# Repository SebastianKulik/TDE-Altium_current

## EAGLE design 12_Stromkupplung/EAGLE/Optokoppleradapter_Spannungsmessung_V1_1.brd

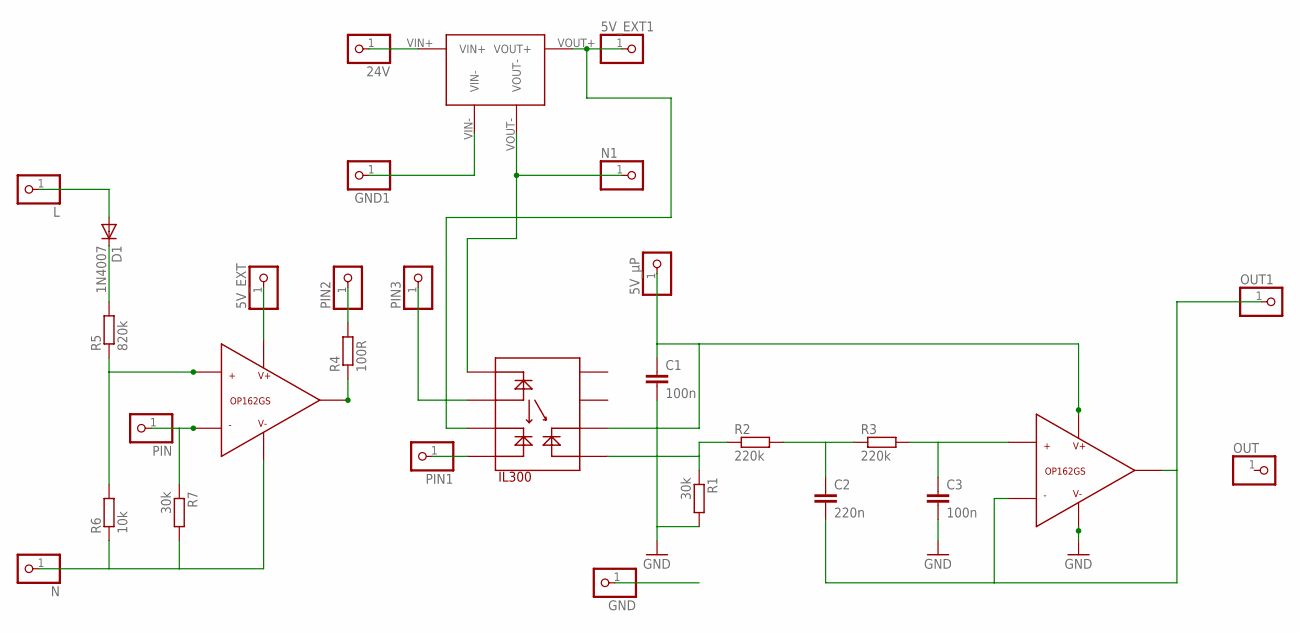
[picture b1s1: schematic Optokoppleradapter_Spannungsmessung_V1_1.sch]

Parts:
5V_EXT, 5V_EXT1, 5V_µP, 24V: PINHD-1X1; 1X01
C1, C3: 100n; C0805
C2: 220n; C0805
D1: 1N4007; DO35-7
GND, GND1: PINHD-1X1; 1X01
L: PINHD-1X1; 1X01
N, N1: PINHD-1X1; 1X01
OUT, OUT1: PINHD-1X1; 1X01
PIN, PIN1, PIN2, PIN3: PINHD-1X1; 1X01
R1: 30k; R0805
R2, R3: 220k; R0805
R4: 100R; R0805
R5: 820k; 0207/7
R6: 10k; 0207/7
R7: 30k; 0207/7
U$1: IL300; DIP8
U$2, U$3: OP162GS; SOIC_N
U$4: RECOM_RO-2405S; 4PIN_SIP

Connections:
5V_EXTERN: 5V_EXT.1, U$2.P$7 (V+)
5V_EXTERN1: 5V_EXT1.1, U$1.P$3, U$4.VOUT+
5V_µP: 5V_µP.1, C1.1, U$1.P$6, U$3.P$7 (V+)
24V: 24V.1, U$4.VIN+
GND: GND.1
GND1: C1.2, C3.2, GND1.1, R1.2, U$3.P$4 (V-), U$4.VIN-
L: D1.A, L.1
N: N.1, R6.1, R7.2, U$2.P$4 (V-)
N1: N1.1, U$1.P$1, U$4.VOUT-
unnamed: D1.C, R5.2
unnamed: R5.1, R6.2, U$2.P$3 (+)
unnamed: PIN1.1, U$1.P$4
unnamed: PIN.1, R7.1, U$2.P$2 (-)
unnamed: R4.1, U$2.P$6 (OUT)
unnamed: PIN2.1, R4.2
unnamed: PIN3.1, U$1.P$2
unnamed: R1.1, R2.1, U$1.P$5
unnamed: C2.1, R2.2, R3.1
unnamed: C3.1, R3.2, U$3.P$3 (+)
OUT1: C2.2, OUT1.1, U$3.P$2 (-), U$3.P$6 (OUT)

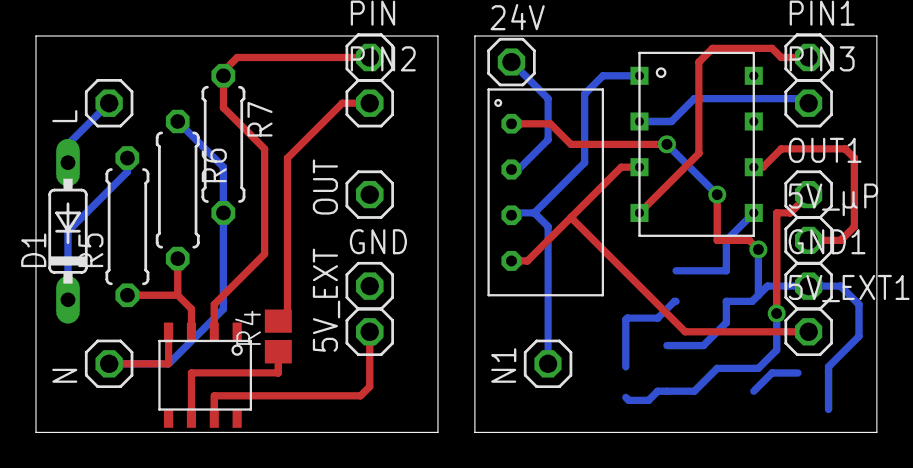
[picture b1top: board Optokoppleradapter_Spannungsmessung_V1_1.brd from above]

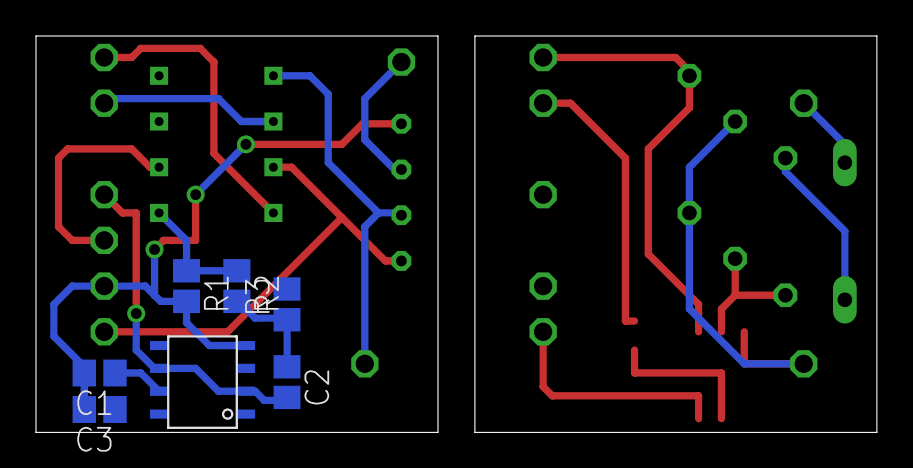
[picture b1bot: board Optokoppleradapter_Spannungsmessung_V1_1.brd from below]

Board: 2 copper layers, 46.7 x 22.0 mm, 30 parts (7 on the bottom side), 19 nets.

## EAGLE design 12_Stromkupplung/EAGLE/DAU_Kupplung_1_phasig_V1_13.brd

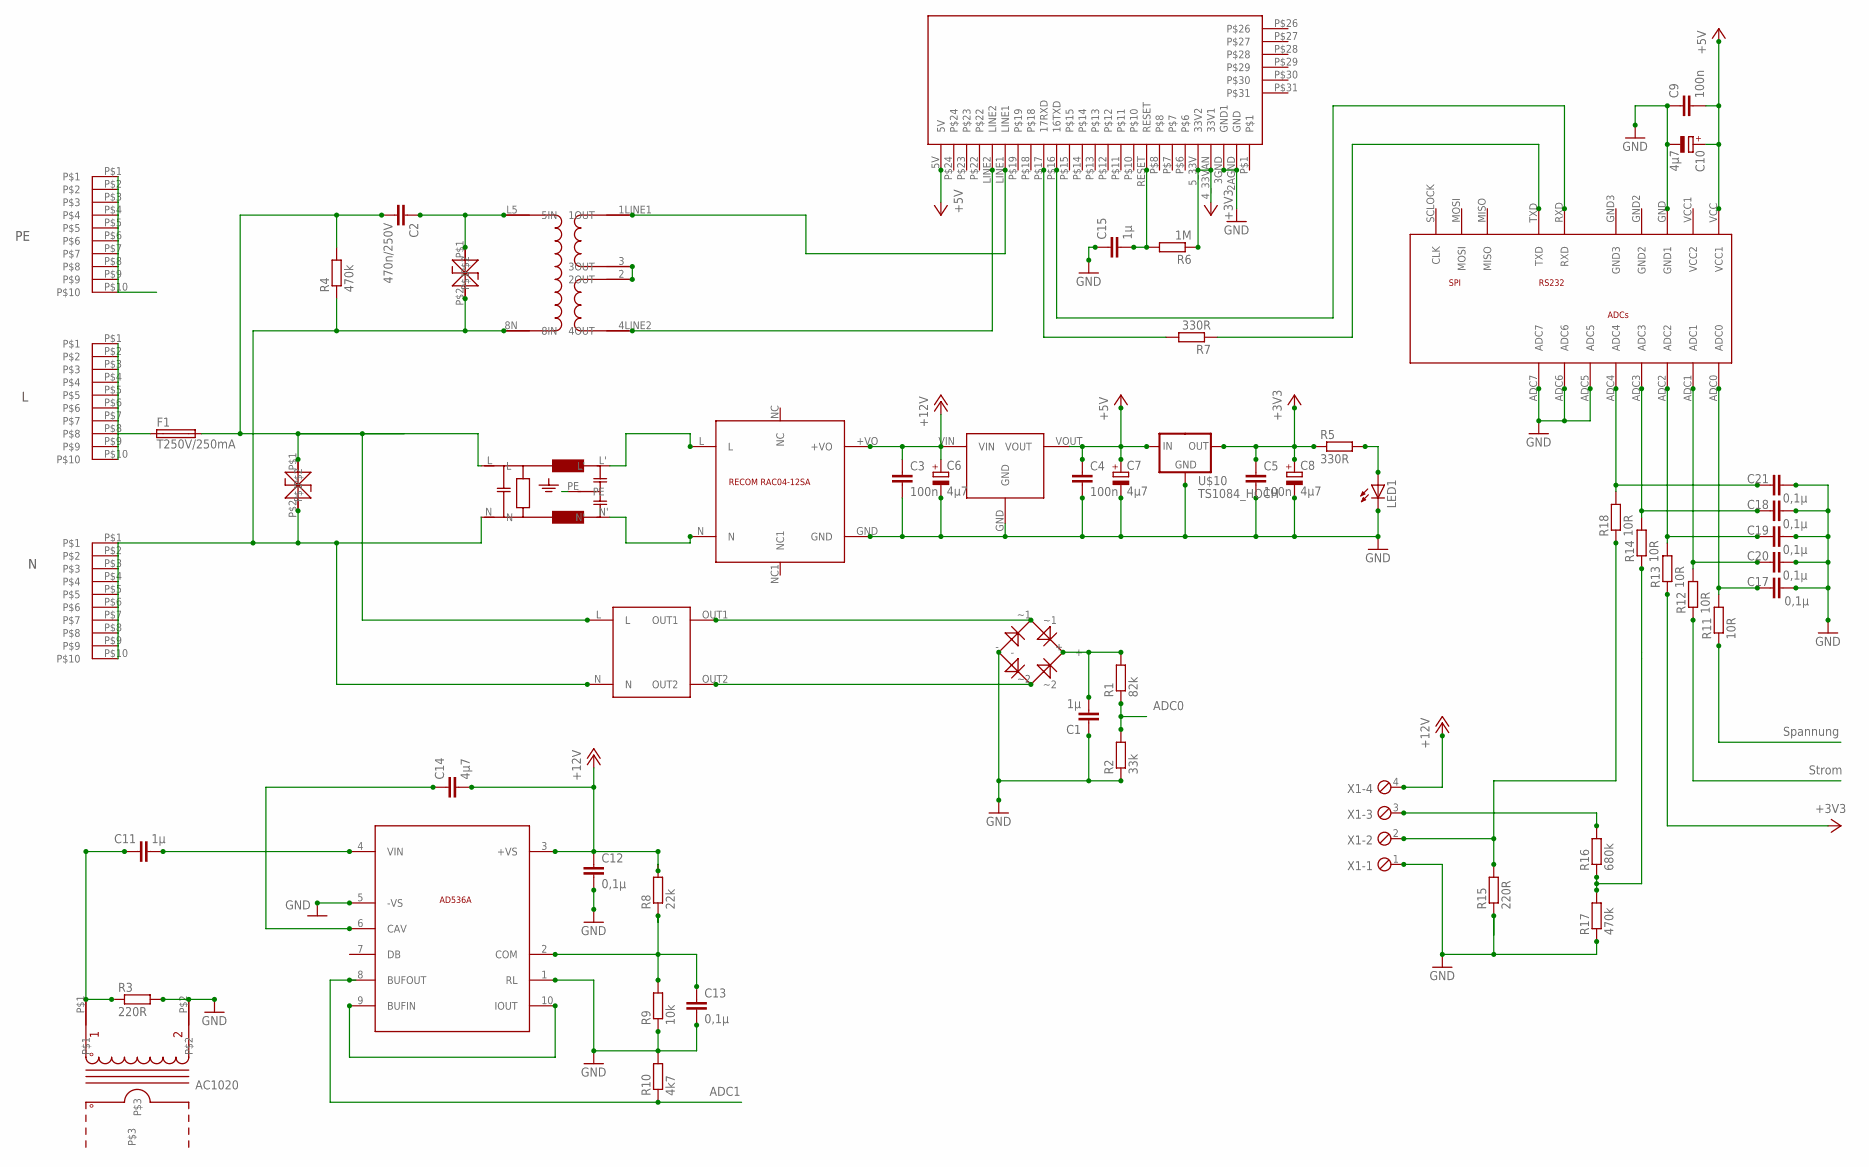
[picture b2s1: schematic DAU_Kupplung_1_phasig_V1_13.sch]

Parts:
AC1020: AC1010
C1: 1µ; C2.5-3
C2: 470n/250V; C150-072X183
C3, C4, C5, C9: 100n; C0805
C6, C7, C8, C10: 4µ7; E2-4
C11, C15: 1µ; C0805
C12, C13, C17, C18, C19, C20, C21: 0,1µ; C0805
C14: 4µ7; C0805
F1: T250V/250mA; TR5
L: PRINT_CONNECTOR; FASTON_DOUBLE
LED1: LEDSQR2X5; LED2X5
N: PRINT_CONNECTOR; FASTON_DOUBLE
PE: PRINT_CONNECTOR; FASTON_DOUBLE
R1: 82k; R1206
R2: 33k; R1206
R3, R15: 220R; R1206
R4: 470k; 0204/7
R5, R7: 330R; R1206
R6: 1M; R1206
R8: 22k; R1206
R9: 10k; R1206
R10: 4k7; R1206
R11, R12, R13, R14, R18: 10R; R1206
R16: 680k; R1206
R17: 470k; R1206
U$1: RECOM_RAC04_12SA; RAC04_12SA
U$2: SICHERHEITSTRAFO; TRAFO_0,35VA
U$3: ADUC831_MINIMUM; ADUC_MINIMUM
U$4: IT800
U$5: PLC_UEBERTRAGER_V2; PLC-UEBERTRAGER_V2
U$6: NETZFILTER_05_A; NETZFILTER
U$7: AD536; TO100_10PIN
U$8: RECTIFIER
U$9, U$12: TSV
U$10: TS1084_HOCH
U$11: RECOM_785_05; RECOM785X
X1: MPT4; 4POL254

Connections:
+3V3: C5.1, C8.+, R5.1, R6.1, R13.1, U$4.4_33VAN (33V1), U$4.5_33V (33V2), U$10.OUT
+5V: C4.1, C7.+, C9.2, C10.+, U$3.VCC (VCC1), U$4.5V, U$10.IN, U$11.VOUT
+12V: C3.1, C6.+, C12.1, C14.2, R8.2, U$1.+VO, U$7.3 (+VS), U$11.VIN, X1.4
ADC0: R1.1, R2.2, R11.1
ADC1: R10.1, R12.1, U$7.8 (BUFOUT)
GND: AC1020.P$2, C1.1, C3.2, C4.2, C5.2, C6.-, C7.-, C8.-, C9.1, C10.-, C12.2, C13.2, C15.1, C17.2, C18.2, C19.2, C20.2, C21.2, LED1.K (C), R2.1, R3.2, R9.1, R10.2, R15.1, R17.1, U$1.GND, U$3.ADC5, U$3.ADC6, U$3.ADC7, U$3.GND (GND1), U$4.2AGND (GND), U$4.3GND (GND1), U$7.1 (RL), U$7.5 (-VS), U$8.-, U$10.GND, U$11.GND, X1.1
unnamed: U$5.2 (2OUT), U$5.3 (3OUT)
unnamed: U$7.9 (BUFIN), U$7.10 (IOUT)
unnamed: R7.2, U$4.P$17 (17RXD)
unnamed: U$2.OUT1, U$8.~1
unnamed: U$4.LINE1, U$5.1LINE1 (1OUT)
unnamed: F1.1, L.P$1, L.P$2, L.P$3, L.P$4, L.P$5, L.P$6, L.P$7, L.P$8, L.P$9, L.P$10
unnamed: C1.2, R1.2, U$8.+
unnamed: AC1020.P$1, C11.1, R3.1
unnamed: U$2.OUT2, U$8.~2
unnamed: C11.2, U$7.4 (VIN)
unnamed: C2.1, U$5.L5 (5IN), U$12.P$1
unnamed: U$4.LINE2, U$5.4LINE2 (4OUT)
unnamed: R7.1, U$3.TXD
unnamed: U$3.RXD, U$4.P$16 (16TXD)
unnamed: C14.1, U$7.6 (CAV)
unnamed: C21.1, R18.2, U$3.ADC4
unnamed: U$1.L, U$6.L'
unnamed: LED1.A, R5.2
unnamed: C15.2, R6.2, U$4.RESET
unnamed: C13.1, R8.1, R9.2, U$7.2 (COM)
unnamed: U$1.N, U$6.N'
unnamed: N.P$1, N.P$2, N.P$3, N.P$4, N.P$5, N.P$6, N.P$7, N.P$8, N.P$9, N.P$10, R4.1, U$2.N, U$5.8N (8IN), U$6.N, U$9.P$2, U$12.P$2
unnamed: C2.2, F1.2, R4.2, U$2.L, U$6.L, U$9.P$1
unnamed: C18.1, R14.2, U$3.ADC3
unnamed: C19.1, R13.2, U$3.ADC2
unnamed: C20.1, R12.2, U$3.ADC1
unnamed: C17.1, R11.2, U$3.ADC0
unnamed: R15.2, R18.1, X1.2
unnamed: R16.2, X1.3
unnamed: R14.1, R16.1, R17.2
PE: PE.P$1, PE.P$2, PE.P$3, PE.P$4, PE.P$5, PE.P$6, PE.P$7, PE.P$8, PE.P$9, PE.P$10, U$6.PE

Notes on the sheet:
ADC1
ADC0
Spannung
Strom
AC1020

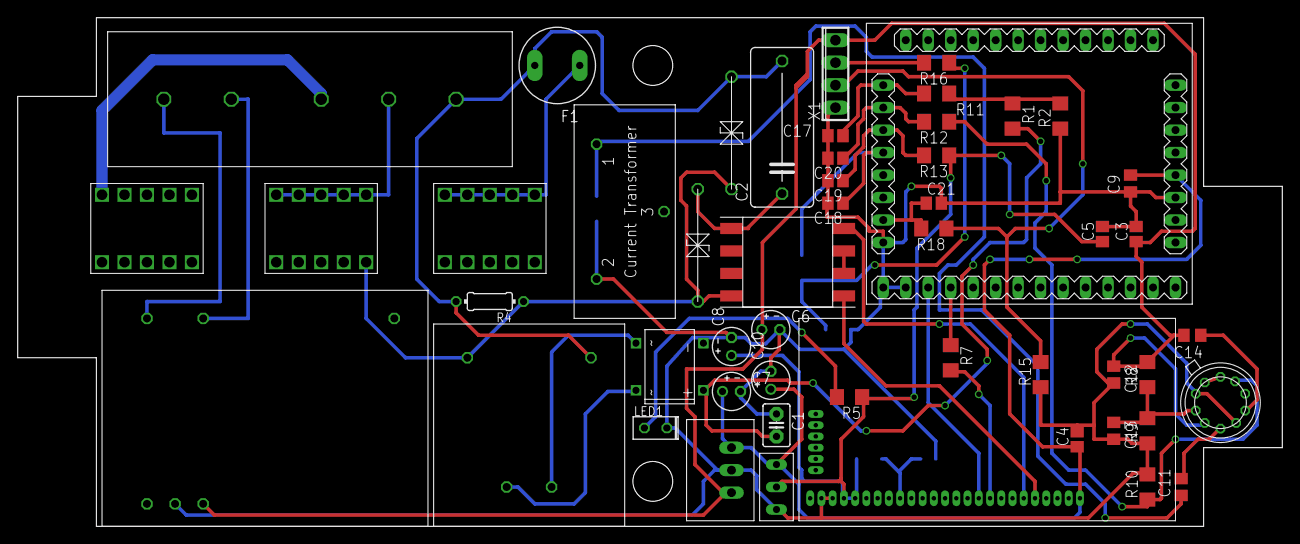
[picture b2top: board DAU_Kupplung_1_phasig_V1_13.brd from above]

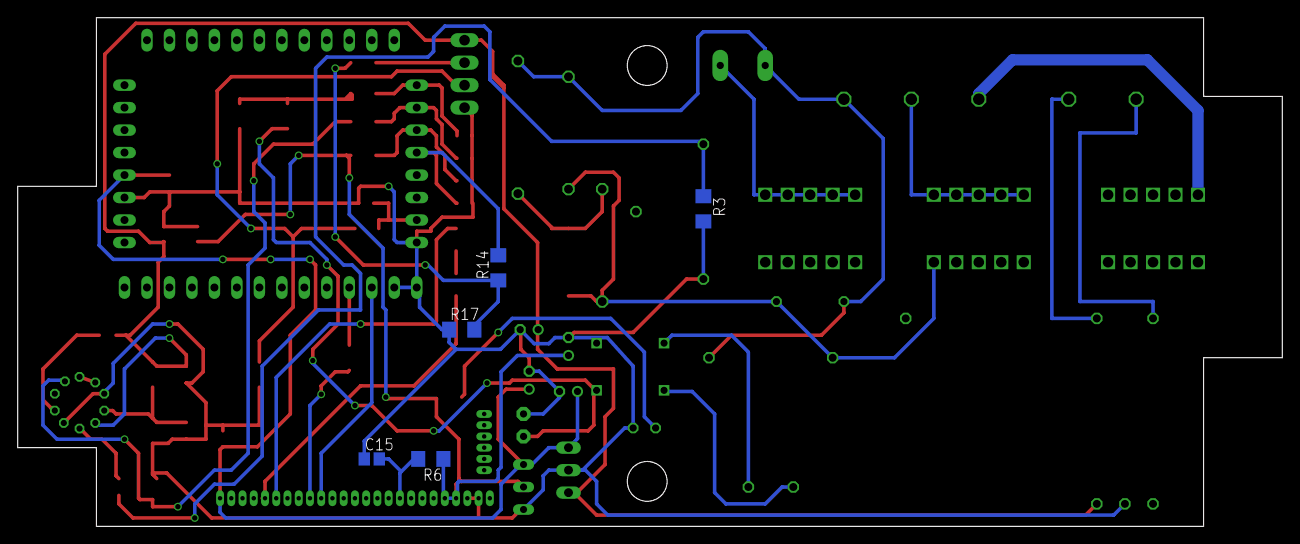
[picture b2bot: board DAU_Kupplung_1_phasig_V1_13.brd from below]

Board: 4 copper layers, 142.9 x 57.5 mm, 57 parts (5 on the bottom side), 37 nets.

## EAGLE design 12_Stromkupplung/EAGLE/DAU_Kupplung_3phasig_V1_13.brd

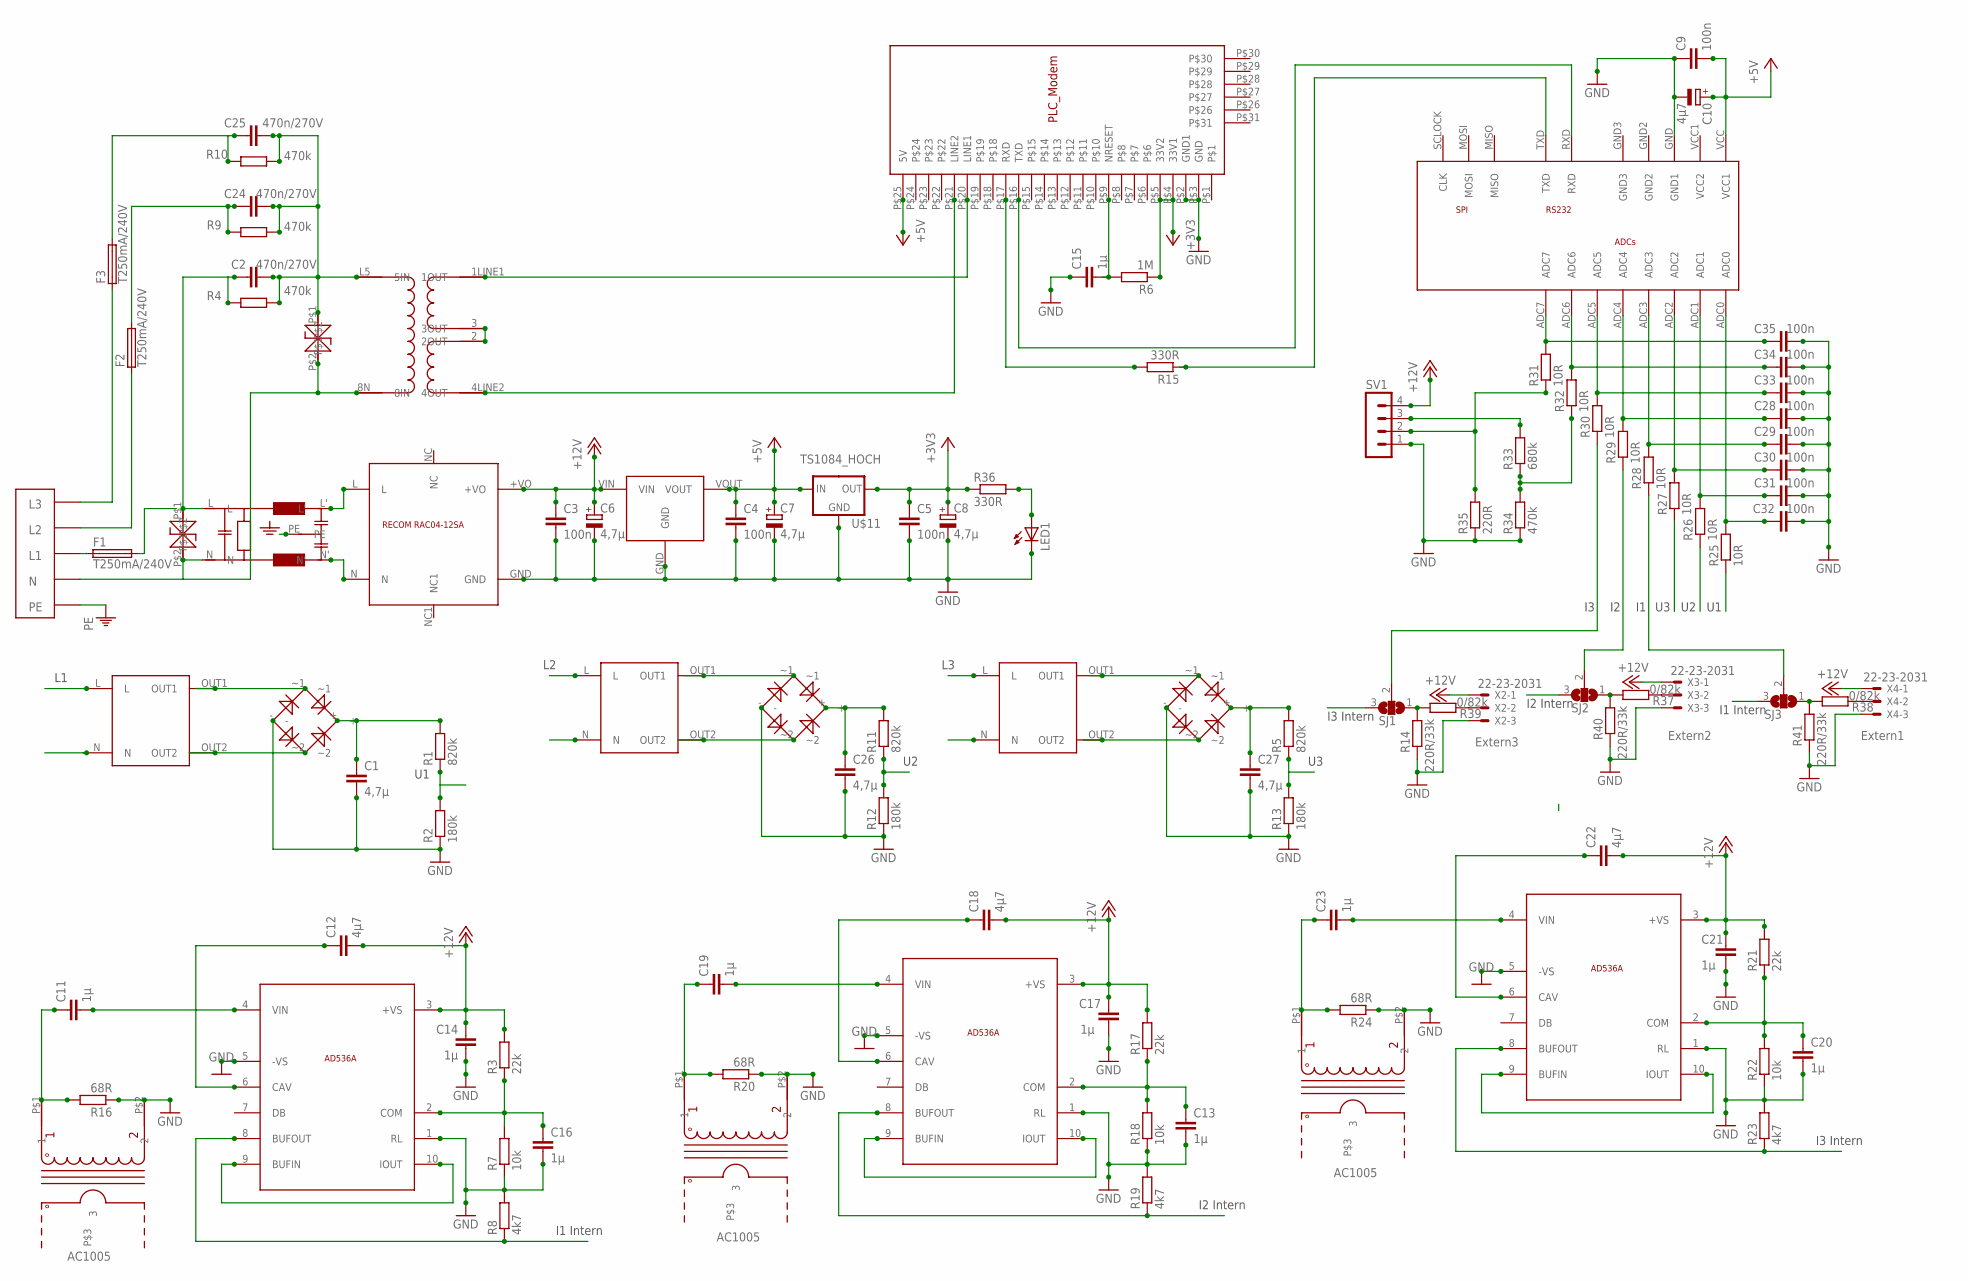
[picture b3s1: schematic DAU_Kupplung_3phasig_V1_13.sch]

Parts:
AC1002_1: AC1010
C1, C26, C27: 4,7µ; C1206
C2, C24, C25: 470n/270V; C225-087X268
C3, C4, C5, C9, C28, C29, C30, C31, C32, C33, C34, C35: 100n; C0805K
C6, C7, C8: 4,7µ; E2,5-6
C10: 4µ7; E2,5-6E
C11, C13, C14, C15, C16, C17, C19, C20, C21, C23: 1µ; C0805K
C12, C18, C22: 4µ7; C0805K
F1, F2, F3: T250mA/240V; TR5
LED1: LEDSQR2X5; LED2X5
P6KE300CA: P6KE300CA; TSV
R1, R5, R11: 820k; R0805
R2, R12, R13: 180k; R0805
R3, R17, R21: 22k; R0805
R4, R9, R10: 470k; 0204/7
R6: 1M; R0805
R7, R18, R22: 10k; R0805
R8, R19, R23: 4k7; R0805
R14, R40, R41: 220R/33k; R0805
R15, R36: 330R; R0805
R16, R20, R24: 68R; 0204/7
R25, R26, R27, R28, R29, R30, R31, R32: 10R; R0805
R33: 680k; R0805
R34: 470k; R0805
R35: 220R; R0805
R37, R38, R39: 0/82k; R0805
SJ1, SJ2, SJ3: SJ2WW; SJ_2W
SV1: MA04-1
TSV2: TSV
U$1: RECOM_RAC04_12SA; RAC04_12SA
U$2, U$16, U$18: SICHERHEITSTRAFO; TRAFO_0,35VA
U$3: ADUC831_MINIMUM; ADUC_MINIMUM
U$4: MODEMSTECKER; MODEM_FUSS
U$5: PLC_UEBERTRAGER_V2; PLC-UEBERTRAGER_V2
U$7, U$14: AC1010
U$8, U$17, U$19: RECTIFIER
U$10: RECOM_785_05; RECOM785X
U$11: TS1084_HOCH
U$12, U$13, U$15: AD536; TO100_10PIN
U$20: NETZFILTER_05_A; NETZFILTER
X1: CONNECTO_5_POL; CONNECTOR_5_POL
X2, X3, X4: 22-23-2031

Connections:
+3V3: C5.1, C8.+, R6.1, R36.1, U$4.P$4 (33V1), U$4.P$5 (33V2), U$11.OUT
+5V: C4.1, C7.+, C9.2, C10.+, U$3.VCC (VCC1), U$4.P$25 (5V), U$10.VOUT, U$11.IN
+12V: C3.1, C6.+, C12.2, C14.2, C17.2, C18.2, C21.1, C22.2, R3.2, R17.2, R21.2, SV1.4, U$1.+VO, U$10.VIN, U$12.3 (+VS), U$13.3 (+VS), U$15.3 (+VS), X2.1, X3.1, X4.1
ADC0: C32.1, R25.2, U$3.ADC0
ADC1: C31.1, R26.2, U$3.ADC1
ADC2: C30.1, R27.2, U$3.ADC2
ADC3: C29.1, R28.2, U$3.ADC3
ADC4: C28.1, R29.2, U$3.ADC4
ADC5: C33.1, R30.2, U$3.ADC5
GND: AC1002_1.P$2 (2), C1.2, C3.2, C4.2, C5.2, C6.-, C7.-, C8.-, C9.1, C10.-, C13.2, C14.1, C15.1, C16.2, C17.1, C20.2, C21.2, C26.2, C27.2, C28.2, C29.2, C30.2, C31.2, C32.2, C33.2, C34.2, C35.2, LED1.K (C), R2.1, R7.1, R8.2, R12.1, R13.1, R14.1, R16.1, R18.1, R19.2, R20.1, R22.1, R23.2, R24.1, R34.1, R35.1, R40.1, R41.1, SV1.1, U$1.GND, U$3.GND (GND1), U$4.P$2 (GND1), U$4.P$3 (GND), U$7.P$2 (2), U$8.-, U$10.GND, U$11.GND, U$12.1 (RL), U$12.5 (-VS), U$13.1 (RL), U$13.5 (-VS), U$14.P$2 (2), U$15.1 (RL), U$15.5 (-VS), U$17.-, U$19.-, X2.3, X3.3, X4.3
I1: R28.1, SJ3.2
I1INTERN: R8.1, SJ3.3, U$13.8 (BUFOUT)
I2: R29.1, SJ2.2
I2INTERN: R19.1, SJ2.3, U$12.8 (BUFOUT)
I3: R30.1, SJ1.2
I3INTERN: R23.1, SJ1.3, U$15.8 (BUFOUT)
L1: C2.1, F1.2, P6KE300CA.P$1, R4.2, U$2.L, U$20.L
L2: C24.1, F2.2, R9.2, U$16.L
L3: C25.1, F3.2, R10.2, U$18.L
N: P6KE300CA.P$2, TSV2.P$2, U$2.N, U$5.8N (8IN), U$16.N, U$18.N, U$20.N, X1.P$4
unnamed: R15.2, U$4.P$17 (RXD)
unnamed: AC1002_1.P$1 (1), C11.1, R16.2
unnamed: C11.2, U$13.4 (VIN)
unnamed: U$2.OUT1, U$8.~1
unnamed: U$4.P$20 (LINE1), U$5.1LINE1 (1OUT)
unnamed: U$13.9 (BUFIN), U$13.10 (IOUT)
unnamed: C1.1, R1.2, U$8.+
unnamed: C35.1, R31.2, U$3.ADC7
unnamed: U$2.OUT2, U$8.~2
unnamed: C26.1, R11.2, U$17.+
unnamed: U$16.OUT1, U$17.~1
unnamed: U$16.OUT2, U$17.~2
unnamed: U$4.P$21 (LINE2), U$5.4LINE2 (4OUT)
unnamed: R15.1, U$3.TXD
unnamed: U$3.RXD, U$4.P$16 (TXD)
unnamed: U$1.L, U$20.L'
unnamed: C16.1, R3.1, R7.2, U$13.2 (COM)
unnamed: LED1.A, R36.2
unnamed: C15.2, R6.2, U$4.P$9 (NRESET)
unnamed: C12.1, U$13.6 (CAV)
unnamed: C19.1, R20.2, U$7.P$1 (1)
unnamed: C19.2, U$12.4 (VIN)
unnamed: U$12.9 (BUFIN), U$12.10 (IOUT)
unnamed: C34.1, R32.2, U$3.ADC6
unnamed: C2.2, C24.2, C25.2, R4.1, R9.1, R10.1, TSV2.P$1, U$5.L5 (5IN)
unnamed: C13.1, R17.1, R18.2, U$12.2 (COM)
unnamed: C18.1, U$12.6 (CAV)
unnamed: C23.1, R24.2, U$14.P$1 (1)
unnamed: C23.2, U$15.4 (VIN)
unnamed: U$15.9 (BUFIN), U$15.10 (IOUT)
unnamed: U$5.2 (2OUT), U$5.3 (3OUT)
unnamed: C27.1, R5.2, U$19.+
unnamed: U$18.OUT1, U$19.~1
unnamed: U$18.OUT2, U$19.~2
unnamed: R33.2, SV1.3
unnamed: C20.1, R21.1, R22.2, U$15.2 (COM)
unnamed: C22.1, U$15.6 (CAV)
unnamed: U$1.N, U$20.N'
unnamed: R37.2, R40.2, SJ2.1
unnamed: R37.1, X3.2
unnamed: R14.2, R39.2, SJ1.1
unnamed: F1.1, X1.P$3
unnamed: F2.1, X1.P$2
unnamed: F3.1, X1.P$1
unnamed: R32.1, R33.1, R34.2
unnamed: R31.1, R35.2, SV1.2
unnamed: R39.1, X2.2
unnamed: R38.2, R41.2, SJ3.1
unnamed: R38.1, X4.2
PE: U$20.PE, X1.P$5
U1: R1.1, R2.2, R25.1
U2: R11.1, R12.2, R26.1
U3: R5.1, R13.2, R27.1

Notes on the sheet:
I1 Intern
I2 Intern
I3 Intern
AC1005
Extern1
Extern2
Extern3

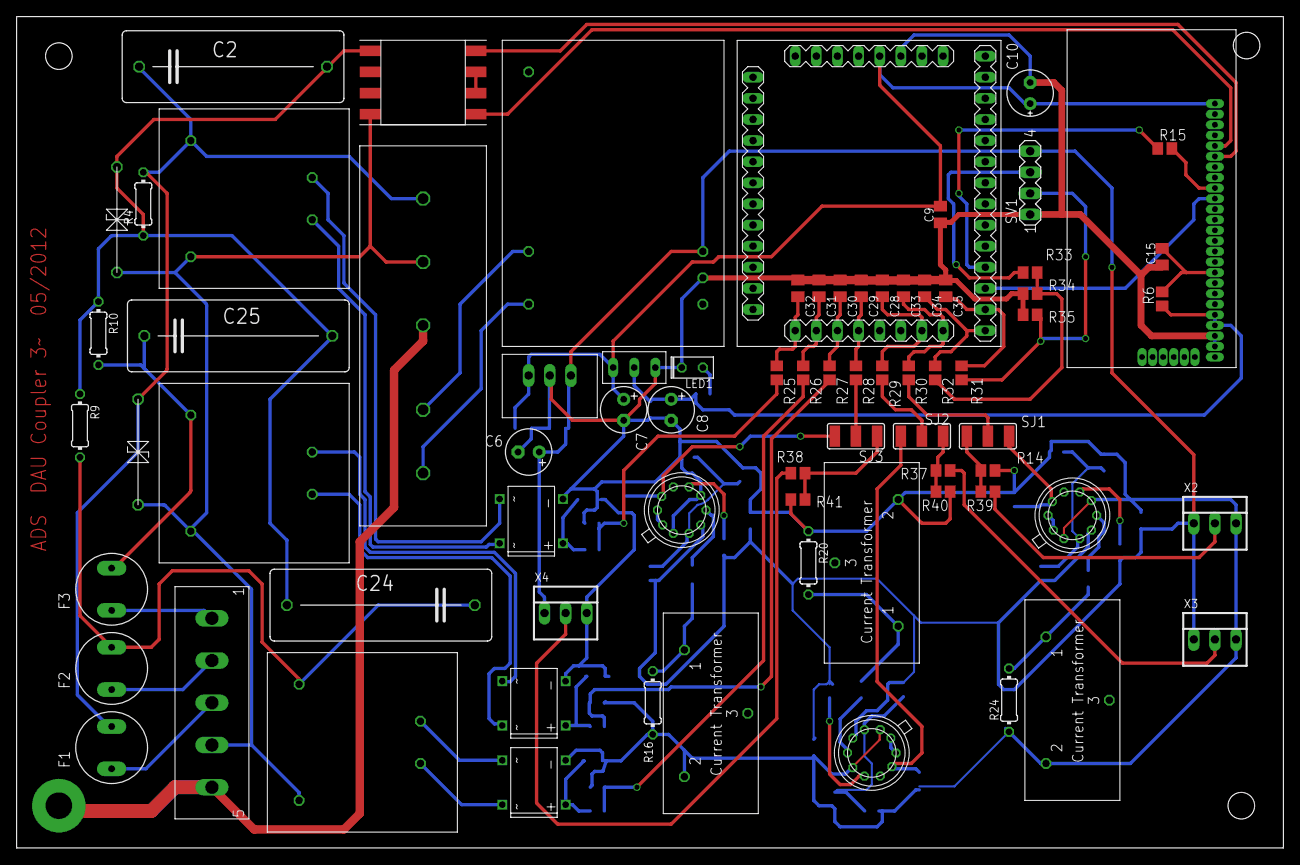
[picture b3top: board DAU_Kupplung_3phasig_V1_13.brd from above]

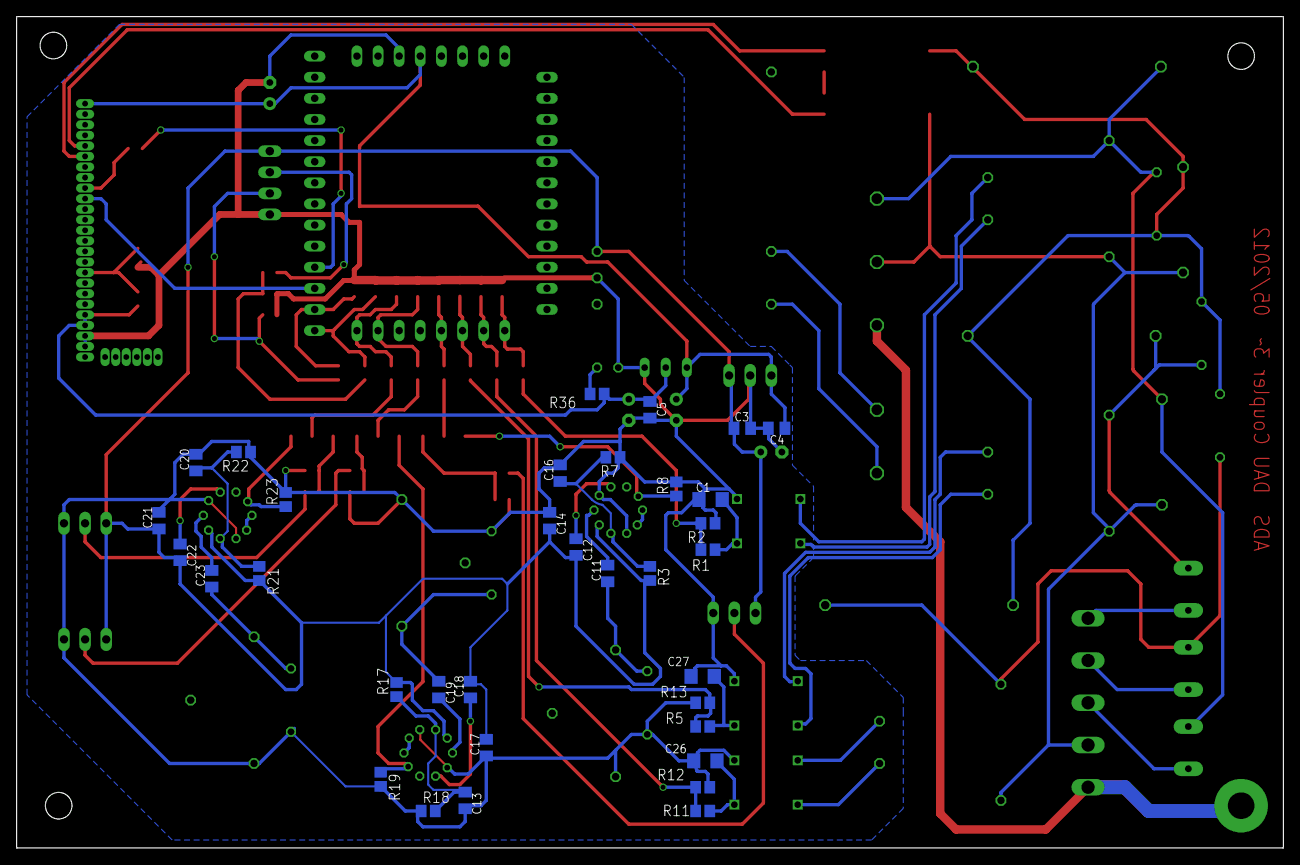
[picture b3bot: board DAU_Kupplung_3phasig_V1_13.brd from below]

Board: 2 copper layers, 152.4 x 100.0 mm, 109 parts (34 on the bottom side), 73 nets.

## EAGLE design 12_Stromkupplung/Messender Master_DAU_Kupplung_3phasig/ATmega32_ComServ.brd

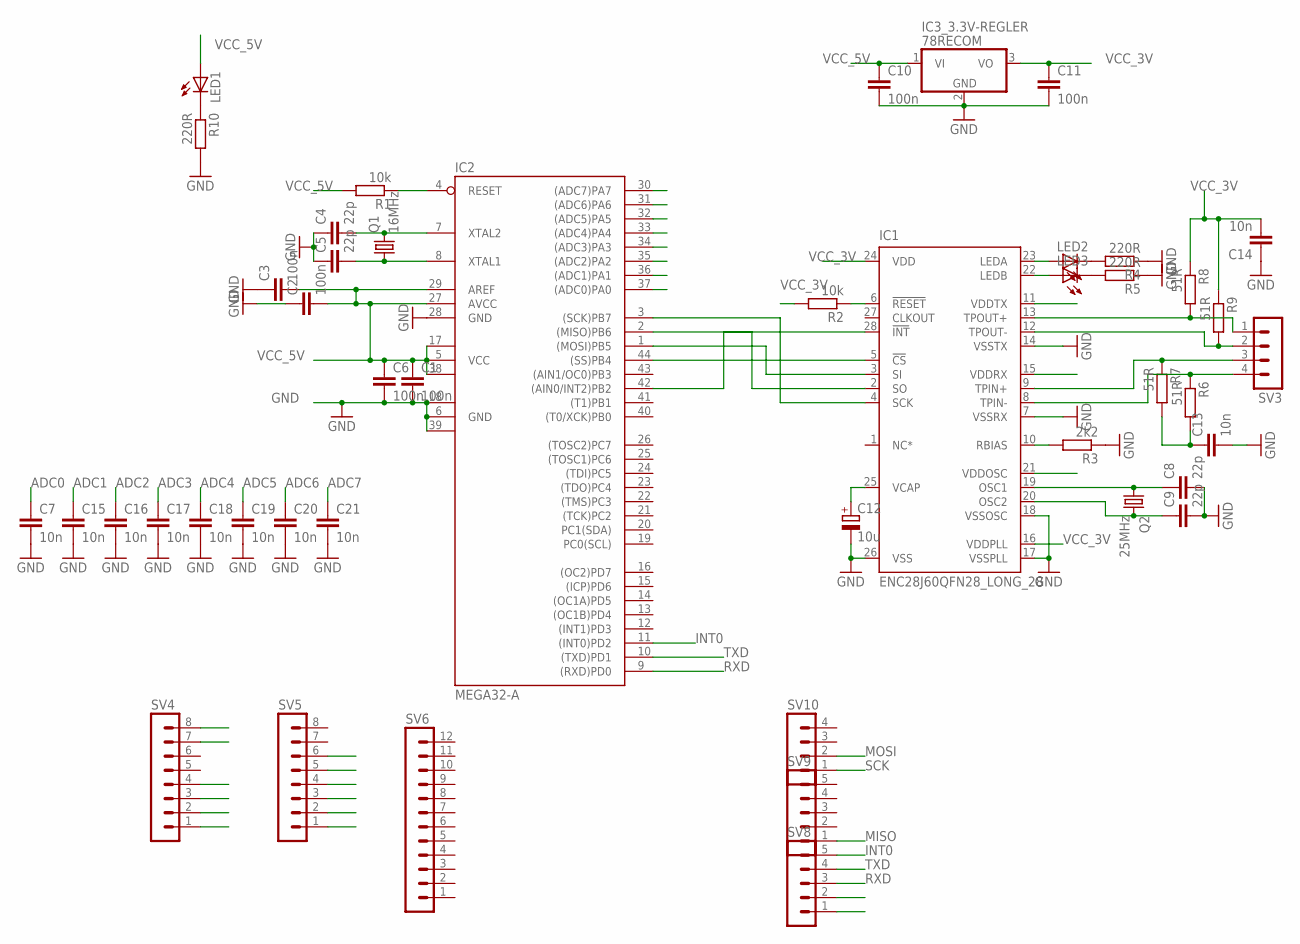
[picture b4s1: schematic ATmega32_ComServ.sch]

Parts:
C1, C2, C3, C6, C10, C11: 100n; C0805
C4, C5, C8, C9: 22p; C0805
C7, C13, C14, C15, C16, C17, C18, C19, C20, C21: 10n; C0805
C12: 10u; SMC_D
IC1: ENC28J60QFN28_LONG_28; QFN28_LONG_ERRLES
IC2: MEGA32-A; TQFP44
IC3_3.3V-REGLER: 78RECOM; RECOM_3POL
LED1, LED2, LED3: LEDCHIPLED_1206; CHIPLED_1206
Q1: 16MHz; HC49/S
Q2: 25MHz; HC49/S
R1, R2: 10k; R1206
R3: 2k2; R1206
R4, R5, R10: 220R; R1206
R6, R8, R9: 51R; R0805
R7: 51R; R1206
SV3, SV10: MA04-1
SV4, SV5: MA08-1
SV6: MA12-1
SV8, SV9: MA05-1

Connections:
1_TD+: IC1.13 (TPOUT+), R8.2, SV3.1
2_TD-: IC1.12 (TPOUT-), R9.2, SV3.2
3_RD+: IC1.9 (TPIN+), R7.1, SV3.3
6_RD-: IC1.8 (TPIN-), R6.1, SV3.4
ADC0: C7.1, IC2.37 ((ADC0)PA0), SV4.1
ADC1: C15.1, IC2.36 ((ADC1)PA1), SV4.2
ADC2: C16.1, IC2.35 ((ADC2)PA2), SV4.3
ADC3: C17.1, IC2.34 ((ADC3)PA3), SV4.4
ADC4: C18.1, IC2.33 ((ADC4)PA4), SV4.7
ADC5: C19.1, IC2.32 ((ADC5)PA5), SV4.8
ADC6: C20.1, IC2.31 ((ADC6)PA6), SV8.1
ADC7: C21.1, IC2.30 ((ADC7)PA7), SV8.2
GND: C1.2, C2.1, C3.1, C4.1, C5.1, C6.2, C7.2, C8.2, C9.2, C10.2, C11.2, C12.-, C13.2, C14.1, C15.2, C16.2, C17.2, C18.2, C19.2, C20.2, C21.2, IC1.7 (VSSRX), IC1.14 (VSSTX), IC1.17 (VSSPLL), IC1.18 (VSSOSC), IC1.26 (VSS), IC2.6 (GND), IC2.18 (GND1), IC2.28 (GND), IC2.39 (GND2), IC3_3.3V-REGLER.2 (GND), R3.1, R4.1, R5.1, R10.2, SV5.2, SV5.3, SV5.6
INT0: IC2.11 ((INT0)PD2), SV8.5
MISO: IC1.2 (SO), IC2.2 ((MISO)PB6), SV9.1
MOSI: IC1.3 (SI), IC2.1 ((MOSI)PB5), SV10.2
unnamed: C5.2, IC2.8 (XTAL1), Q1.1
unnamed: C4.2, IC2.7 (XTAL2), Q1.2
unnamed: LED1.C, R10.1
unnamed: C8.1, IC1.19 (OSC1), Q2.1
unnamed: C9.1, IC1.20 (OSC2), Q2.2
unnamed: C12.+, IC1.25 (VCAP)
unnamed: IC1.28 (!INT), IC2.42 ((AIN0/INT2)PB2)
unnamed: IC1.6 (!RESET), R2.1
unnamed: IC1.10 (RBIAS), R3.2
unnamed: LED2.C, R4.2
unnamed: IC1.23 (LEDA), LED2.A
unnamed: IC1.22 (LEDB), LED3.A
unnamed: LED3.C, R5.2
unnamed: C13.1, R6.2, R7.2
RESET: IC2.4 (RESET), R1.1, SV5.1
RXD: IC2.9 ((RXD)PD0), SV8.3
SCK: IC1.4 (SCK), IC2.3 ((SCK)PB7), SV10.1
SS: IC1.5 (!CS), IC2.44 ((SS)PB4)
TXD: IC2.10 ((TXD)PD1), SV8.4
VCC_3V: C11.1, C14.2, IC1.11 (VDDTX), IC1.15 (VDDRX), IC1.16 (VDDPLL), IC1.21 (VDDOSC), IC1.24 (VDD), IC3_3.3V-REGLER.3 (VO), R2.2, R8.1, R9.1
VCC_5V: C1.1, C2.2, C3.2, C6.1, C10.1, IC2.5 (VCC), IC2.17 (VCC1), IC2.27 (AVCC), IC2.29 (AREF), IC2.38 (VCC2), IC3_3.3V-REGLER.1 (VI), LED1.A, R1.2, SV5.4, SV5.5

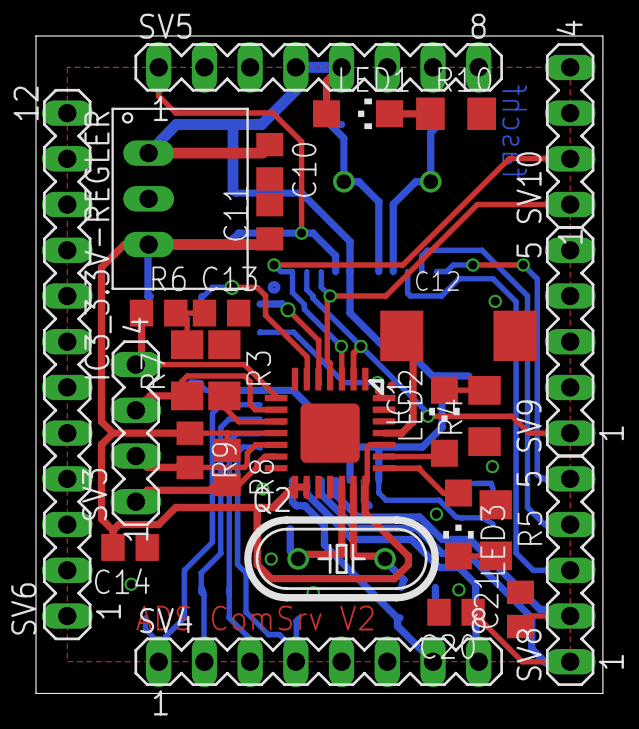
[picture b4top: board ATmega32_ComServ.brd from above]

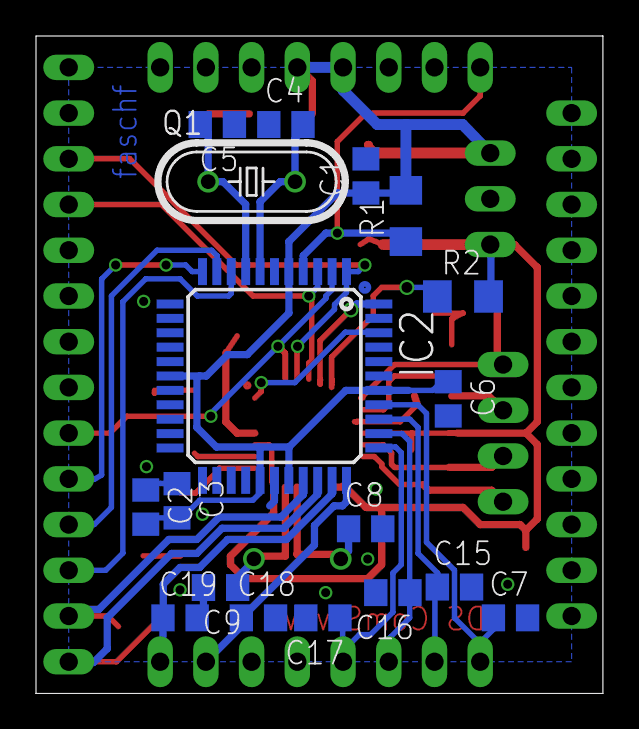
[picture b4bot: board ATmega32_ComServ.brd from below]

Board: 2 copper layers, 31.5 x 36.5 mm, 46 parts (18 on the bottom side), 37 nets.

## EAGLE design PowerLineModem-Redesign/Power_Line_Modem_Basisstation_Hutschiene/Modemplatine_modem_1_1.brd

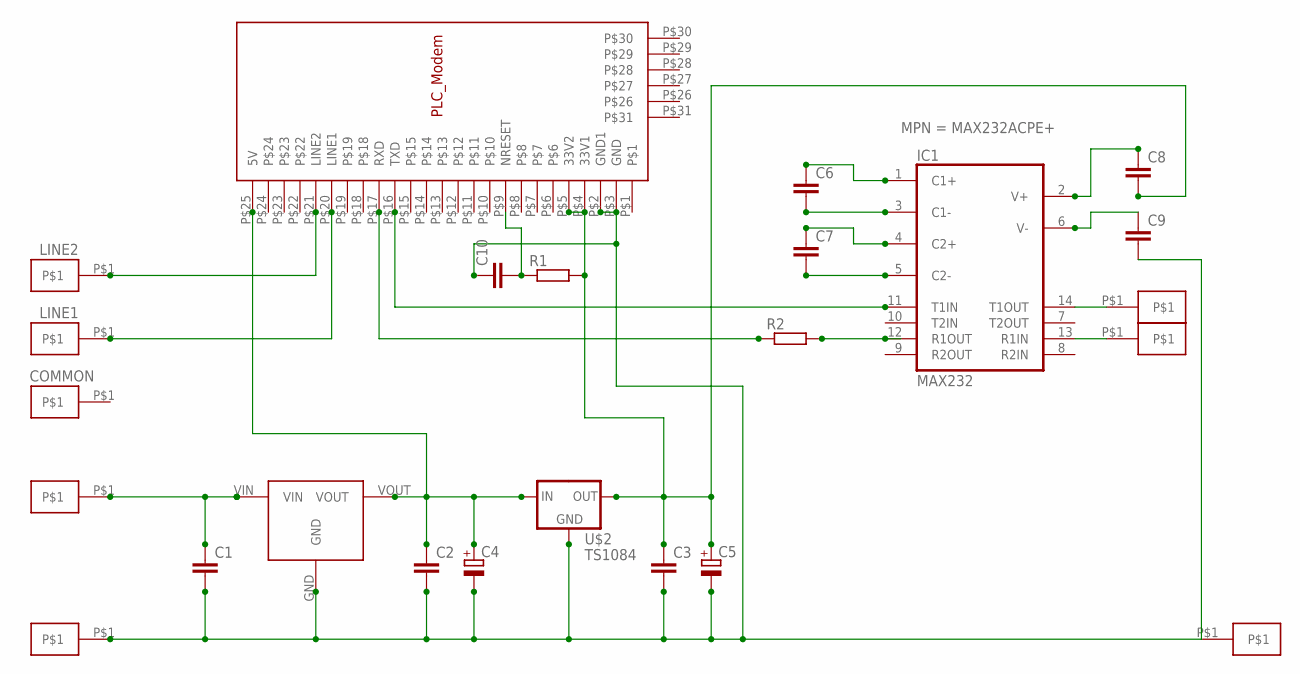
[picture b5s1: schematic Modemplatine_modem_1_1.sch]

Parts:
C1, C2, C3: C2.5/5; C2.5-5
C4, C5: CPOL-EUE2.5-5; E2,5-5
C6, C7, C8, C9, C10: C-EU025-040X050; C025-040X050
IC1: MAX232; DIL16; MPN MAX232ACPE+
LINE1, LINE2: PN4; PIN2
R1, R2: R-EU_0207/10; 0207/10
U$1: RECOM_785_05; RECOM785X
U$2: TS1084
U$3: MODEMSTECKER; MODEM_FUSS
U$4, U$5, U$6, U$7, U$8, U$11: PN4; PIN2

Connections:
GND: IC1.15 (GND)
unnamed: C1.1, U$1.VIN, U$5.P$1
unnamed: C1.2, C2.2, C3.2, C4.-, C5.-, C9.2, C10.1, U$1.GND, U$2.1GND (GND), U$3.P$2 (GND1), U$3.P$3 (GND), U$4.P$1, U$8.P$1
unnamed: C2.1, C4.+, U$1.VOUT, U$2.3IN (IN), U$3.P$25 (5V)
unnamed: C3.1, C5.+, C8.2, R1.2, U$2.2OUT (OUT), U$3.P$4 (33V1), U$3.P$5 (33V2)
unnamed: LINE2.P$1, U$3.P$21 (LINE2)
unnamed: LINE1.P$1, U$3.P$20 (LINE1)
unnamed: C6.1, IC1.1 (C1+)
unnamed: C6.2, IC1.3 (C1-)
unnamed: C7.1, IC1.4 (C2+)
unnamed: C7.2, IC1.5 (C2-)
unnamed: C8.1, IC1.2 (V+)
unnamed: C9.1, IC1.6 (V-)
unnamed: IC1.14 (T1OUT), U$6.P$1
unnamed: IC1.13 (R1IN), U$7.P$1
unnamed: IC1.11 (T1IN), U$3.P$16 (TXD)
unnamed: IC1.12 (R1OUT), R2.2
unnamed: R2.1, U$3.P$17 (RXD)
unnamed: C10.2, R1.1, U$3.P$9 (NRESET)
VCC: IC1.16 (VCC)

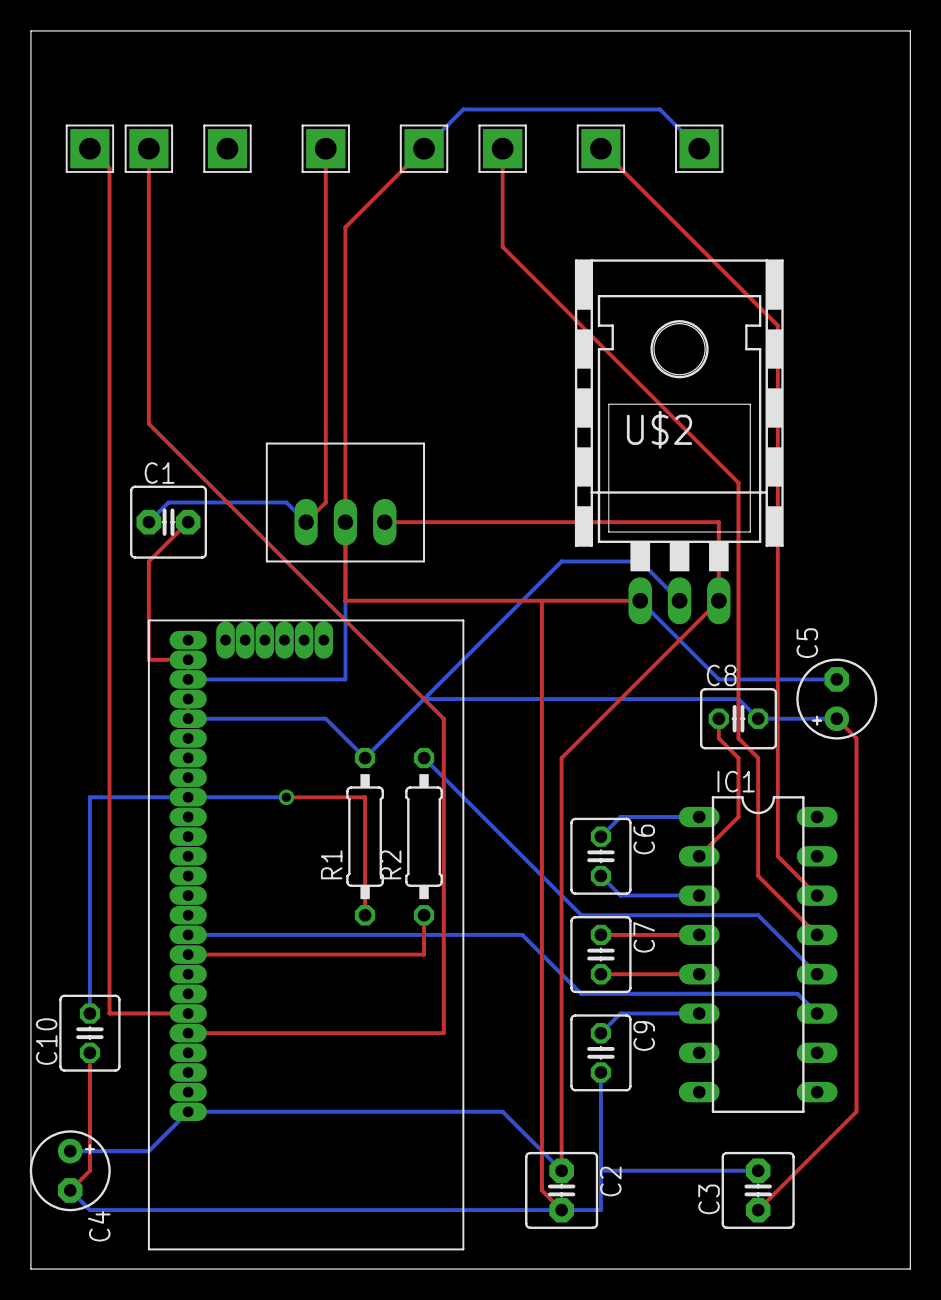
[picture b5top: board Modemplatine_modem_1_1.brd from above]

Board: 2 copper layers, 56.8 x 80.0 mm, 24 parts (0 on the bottom side), 18 nets.

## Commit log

2016-12-16 :space_invader: Added .gitattributes & .gitignore files
2016-12-16 IT-Push-Test
